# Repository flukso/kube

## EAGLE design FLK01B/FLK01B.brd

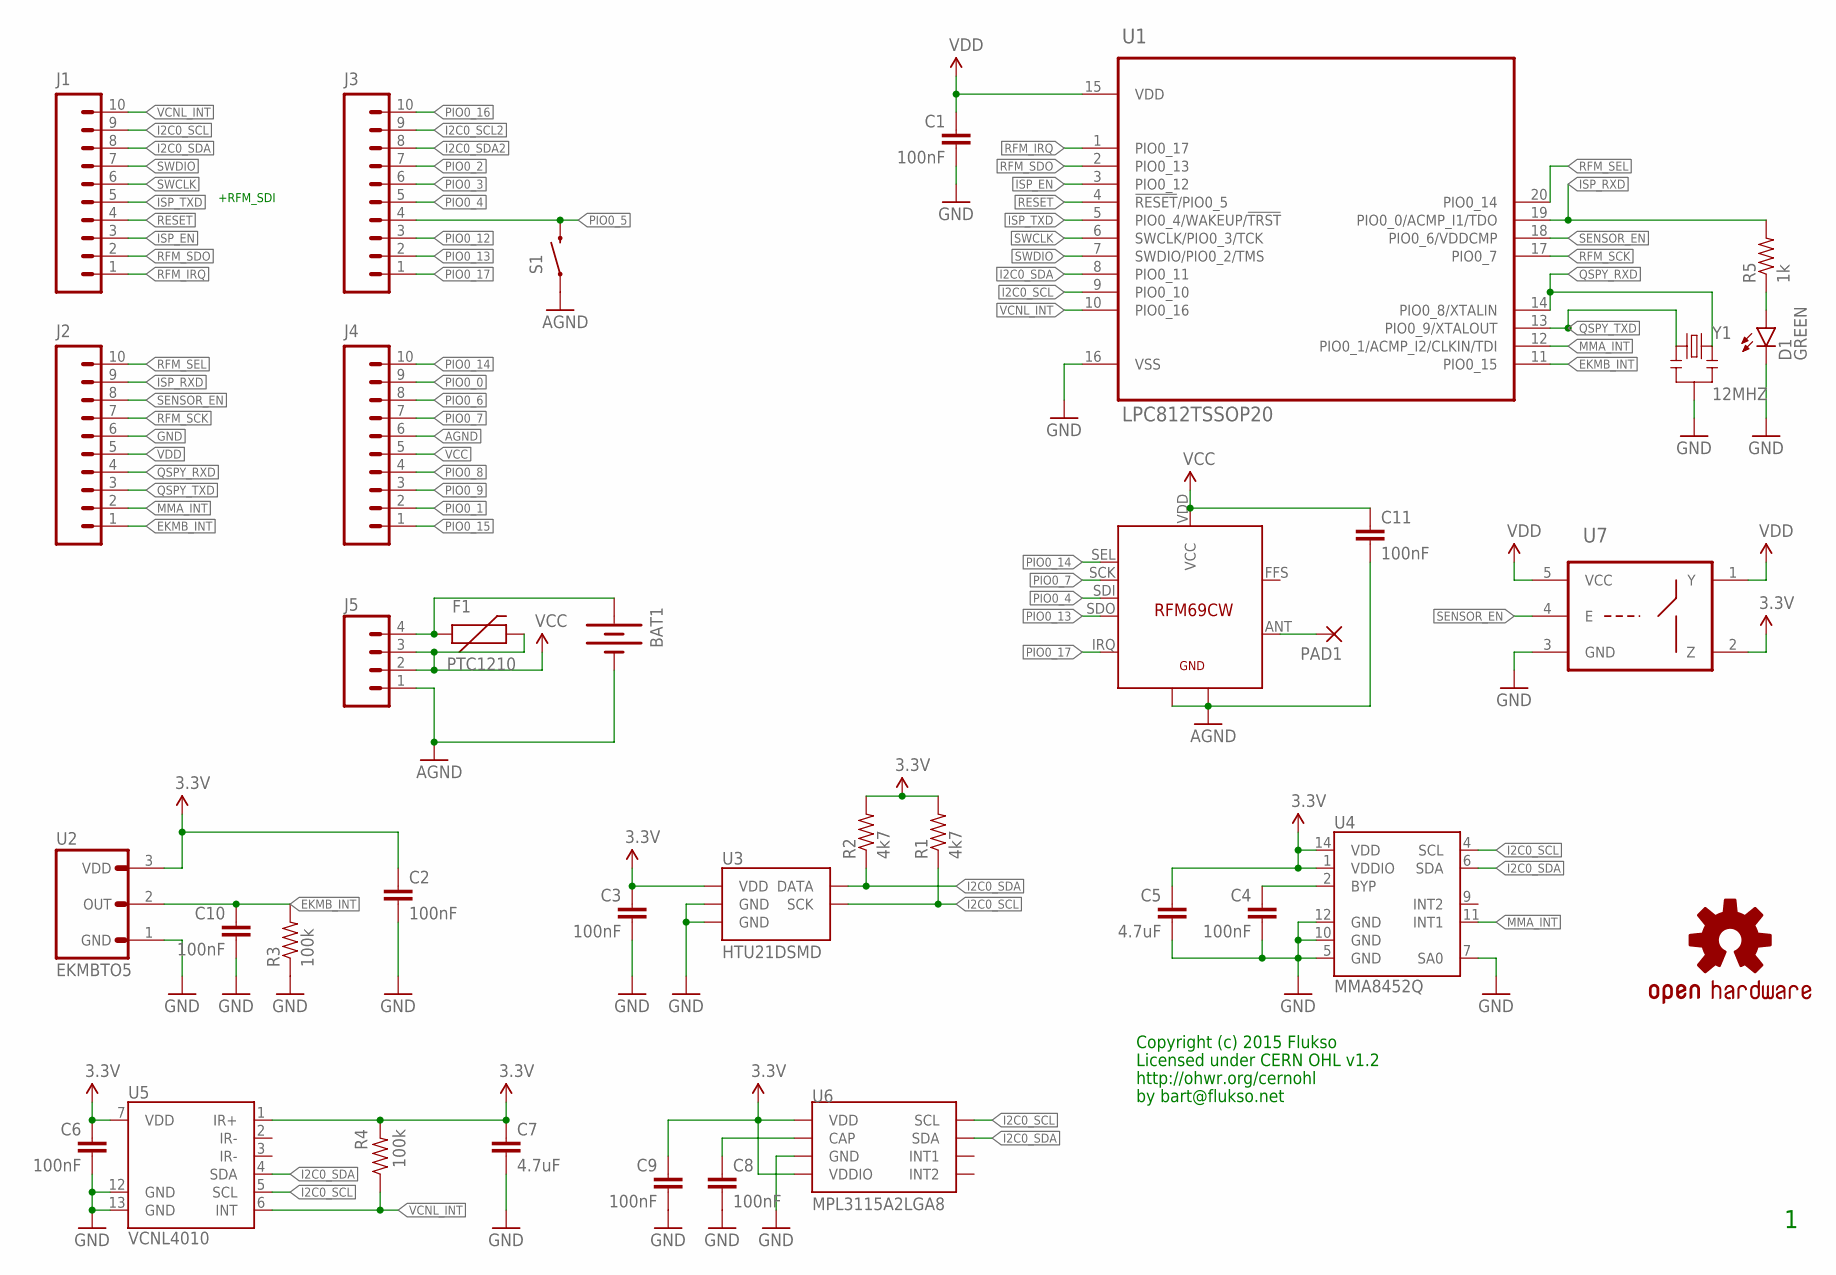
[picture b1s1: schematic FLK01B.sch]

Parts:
BAT1: BATTERY245PTH; BATTCON_245MM_PTH
C1, C2, C3, C4, C6, C8, C9, C10, C11: 100nF; 0402-CAP
C5, C7: 4.7uF; C0805K
D1: GREEN; LED-0603
F1: PTC1210; 1210
J1, J2: M10SMD_MALE_SHORT; 1X10_SMD_MALE_SHORT
J3, J4: M10SMD_FEMALE_SHORT; 1X10_SMD_FEMALE_SHORT
J5: M041X04_NO_SILK; 1X04_NO_SILK
PAD1: WIREPAD_1,6/0,8
R1, R2: 4k7; 0402-RES
R3, R4: 100k; 0402-RES
R5: 1k; 0402-RES
S1: SWITCH-MOMENTARY-2SMD; TACTILE_SWITCH_SMD
U1: LPC812TSSOP20; TSSOP20
U2: EKMBTO5; TO5
U3: HTU21DSMD; HTU21D
U4: MMA8452Q; QFN-16_0.5MM
U5: VCNL4010
U6: MPL3115A2LGA8; LGA8
U7: 741G66; SOT353
U$3: RFM69CW
U$7: OSHW-LOGOS; OSHW-LOGO-S
Y1: 12MHZ; RESONATOR-SMD

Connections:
3.3V: C2.1, C3.1, C5.1, C6.1, C7.1, C9.1, R1.2, R2.2, R4.2, U2.3 (VDD), U3.VDD, U4.1 (VDDIO), U4.14 (VDD), U5.1 (IR+), U5.7 (VDD), U6.1 (VDD), U6.4 (VDDIO), U7.2 (Z)
!ISP_EN!: J1.3, U1.3 (PIO0_12)
!RESET!: J1.4, U1.4 (!RESET!/PIO0_5)
AGND: BAT1.2 (-), C11.2, J4.6, J5.1, S1.1, U$3.GND1, U$3.GND2
EKMB_INT: C10.1, J2.1, R3.2, U1.11 (PIO0_15), U2.2 (OUT)
GND: C1.2, C2.2, C3.2, C4.2, C5.2, C6.2, C7.2, C8.2, C9.2, C10.2, D1.C, J2.6, R3.1, U1.16 (VSS), U2.1 (GND), U3.7 (GND), U3.GND, U4.5 (GND), U4.7 (SA0), U4.10 (GND), U4.12 (GND), U5.12 (GND), U5.13 (GND), U6.3 (GND), U7.3 (GND), Y1.2
I2C0_SCL: J1.9, R1.1, U1.9 (PIO0_10), U3.SCK, U4.4 (SCL), U5.5 (SCL), U6.8 (SCL)
I2C0_SCL2: J3.9
I2C0_SDA: J1.8, R2.1, U1.8 (PIO0_11), U3.DATA, U4.6 (SDA), U5.4 (SDA), U6.7 (SDA)
I2C0_SDA2: J3.8
ISP_RXD: J2.9, R5.2, U1.19 (PIO0_0/ACMP_I1/TDO)
ISP_TXD: J1.5, U1.5 (PIO0_4/WAKEUP/!TRST!)
MMA_INT: J2.2, U1.12 (PIO0_1/ACMP_I2/CLKIN/TDI), U4.11 (INT1)
unnamed: PAD1.1, U$3.ANT
unnamed: BAT1.3 (+), F1.1, J5.4
unnamed: C4.1, U4.2 (BYP)
unnamed: C8.1, U6.2 (CAP)
unnamed: D1.A, R5.1
PIO0_0: J4.9
PIO0_1: J4.2
PIO0_2: J3.7
PIO0_3: J3.6
PIO0_4: J3.5, U$3.SDI
PIO0_5: J3.4, S1.3 (2)
PIO0_6: J4.8
PIO0_7: J4.7, U$3.SCK
PIO0_8: J4.4
PIO0_9: J4.3
PIO0_12: J3.3
PIO0_13: J3.2, U$3.SDO
PIO0_14: J4.10, U$3.SEL
PIO0_15: J4.1
PIO0_16: J3.10
PIO0_17: J3.1, U$3.IRQ
QSPY_RXD: J2.4, U1.14 (PIO0_8/XTALIN), Y1.3
QSPY_TXD: J2.3, U1.13 (PIO0_9/XTALOUT), Y1.1
RFM_IRQ: J1.1, U1.1 (PIO0_17)
RFM_SCK: J2.7, U1.17 (PIO0_7)
RFM_SDO: J1.2, U1.2 (PIO0_13)
RFM_SEL: J2.10, U1.20 (PIO0_14)
SENSOR_EN: J2.8, U1.18 (PIO0_6/VDDCMP), U7.4 (E)
SWCLK: J1.6, U1.6 (SWCLK/PIO0_3/TCK)
SWDIO: J1.7, U1.7 (SWDIO/PIO0_2/TMS)
VCC: C11.1, F1.2, J4.5, J5.2, J5.3, U$3.VDD (VCC)
VCNL_INT: J1.10, R4.1, U1.10 (PIO0_16), U5.6 (INT)
VDD: C1.1, J2.5, U1.15 (VDD), U7.1 (Y), U7.5 (VCC)

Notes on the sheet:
Copyright (c) 2015 Flukso
Licensed under CERN OHL v1.2
http://ohwr.org/cernohl
by bart@flukso.net
+RFM_SDI

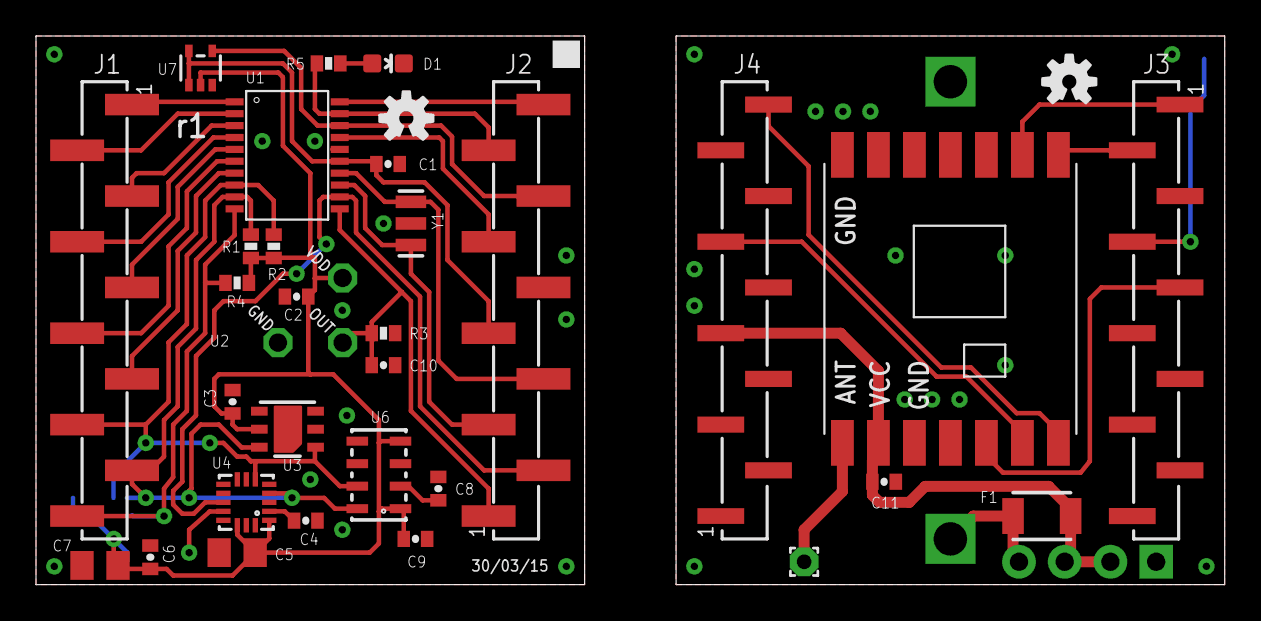
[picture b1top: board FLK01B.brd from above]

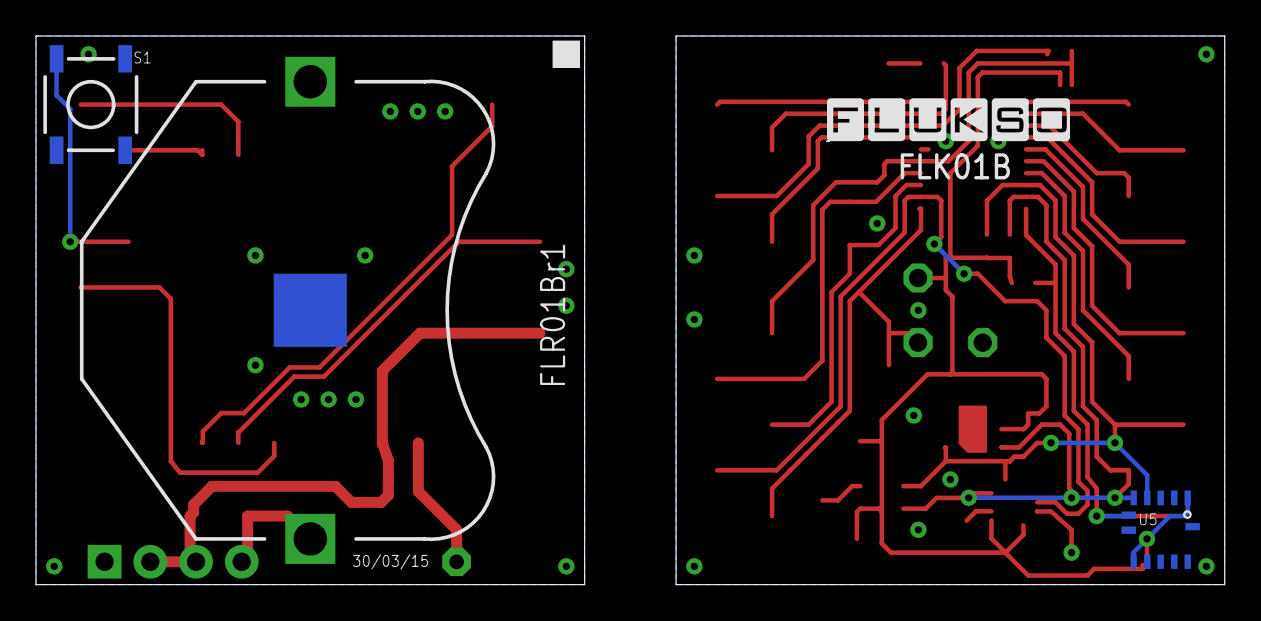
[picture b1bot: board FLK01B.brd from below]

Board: 2 copper layers, 66.0 x 30.5 mm, 38 parts (4 on the bottom side), 34 nets.

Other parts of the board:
U$1: OSHW-LOGOS; OSHW-LOGO-S
U$2: FLUKSO_LOGO_MEDIUM

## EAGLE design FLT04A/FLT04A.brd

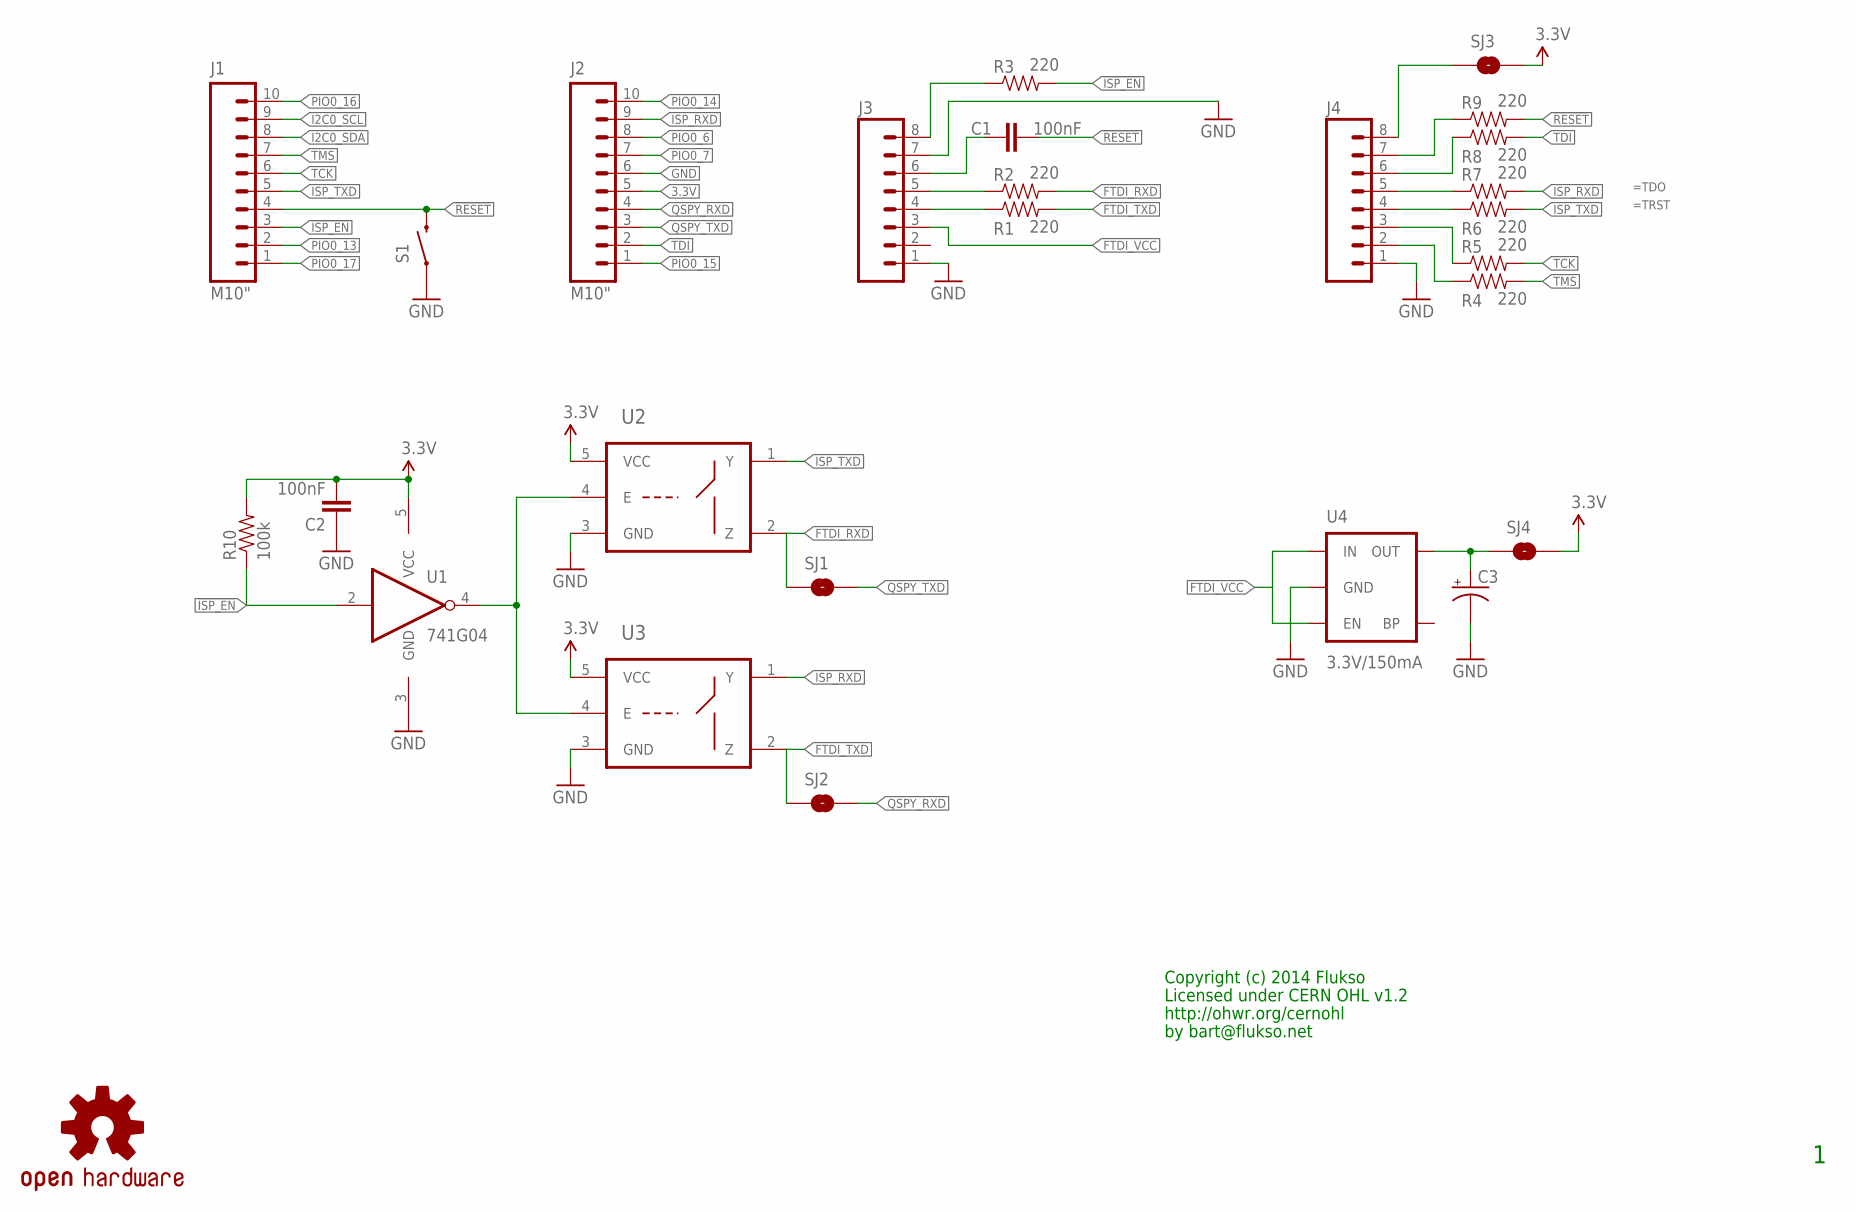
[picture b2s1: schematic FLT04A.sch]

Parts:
C1, C2: 100nF; 0402-CAP
C3: CAP_POL1206; EIA3216
J1, J2: M10"; 1X10
J3, J4: M08; 1X08_PIN1_NO_SILK
R1, R2, R3, R4, R5, R6, R7, R8, R9: 220; 0402-RES
R10: 100k; 0402-RES
S1: SWITCH-MOMENTARY-2SMD; TACTILE_SWITCH_SMD
SJ1, SJ2, SJ3, SJ4: SOLDERJUMPERNC; SJ_2S
U1: 741G04; SOT353
U2, U3: 741G66; SOT353
U4: 3.3V/150mA; SOT23-5
U$1: OSHW-LOGOS; OSHW-LOGO-S

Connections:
3.3V: C2.2, J2.5, R10.2, SJ3.2, SJ4.2, U1.5 (VCC), U2.5 (VCC), U3.5 (VCC)
!ISP_EN!: J1.3, R3.2, R10.1, U1.2 (I)
!RESET!: C1.2, J1.4, R9.2, S1.3 (2)
FTDI_RXD: R2.2, SJ1.1, U2.2 (Z)
FTDI_TXD: R1.2, SJ2.1, U3.2 (Z)
FTDI_VCC: J3.3, U4.1 (IN), U4.3 (EN)
GND: C2.1, C3.C (-), J2.6, J3.1, J3.7, J4.1, S1.1, U1.3 (GND), U2.3 (GND), U3.3 (GND), U4.2 (GND)
I2C0_SCL: J1.9
I2C0_SDA: J1.8
ISP_RXD: J2.9, R7.2, U3.1 (Y)
ISP_TXD: J1.5, R6.2, U2.1 (Y)
unnamed: J3.8, R3.1
unnamed: C1.1, J3.6
unnamed: J3.5, R2.1
unnamed: J3.4, R1.1
unnamed: U1.4 (O), U2.4 (E), U3.4 (E)
unnamed: J4.2, R4.1
unnamed: J4.3, R5.1
unnamed: J4.4, R6.1
unnamed: J4.5, R7.1
unnamed: J4.6, R8.1
unnamed: J4.8, SJ3.1
unnamed: J4.7, R9.1
unnamed: C3.A (+), SJ4.1, U4.5 (OUT)
PIO0_6: J2.8
PIO0_7: J2.7
PIO0_13: J1.2
PIO0_14: J2.10
PIO0_15: J2.1
PIO0_16: J1.10
PIO0_17: J1.1
QSPY_RXD: J2.4, SJ2.2
QSPY_TXD: J2.3, SJ1.2
TCK: J1.6, R5.2
TDI: J2.2, R8.2
TMS: J1.7, R4.2

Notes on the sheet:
Copyright (c) 2014 Flukso
Licensed under CERN OHL v1.2
http://ohwr.org/cernohl
by bart@flukso.net
=TDO
=TRST

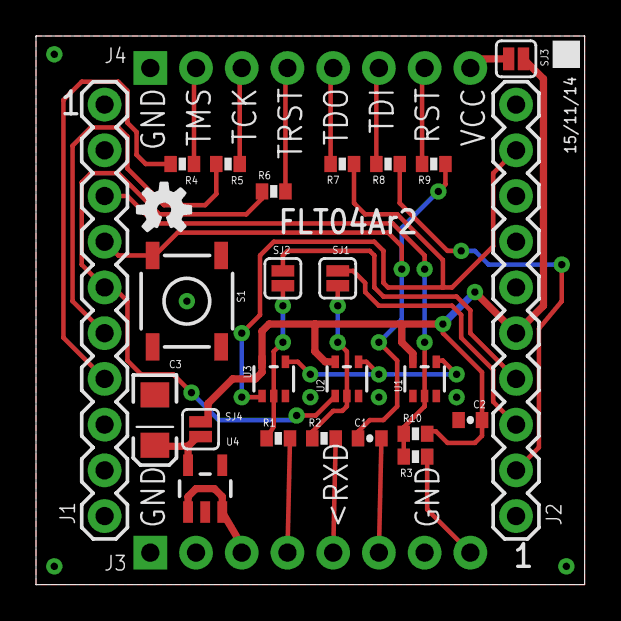
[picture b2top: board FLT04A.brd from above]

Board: 2 copper layers, 30.5 x 30.5 mm, 27 parts (0 on the bottom side), 27 nets.

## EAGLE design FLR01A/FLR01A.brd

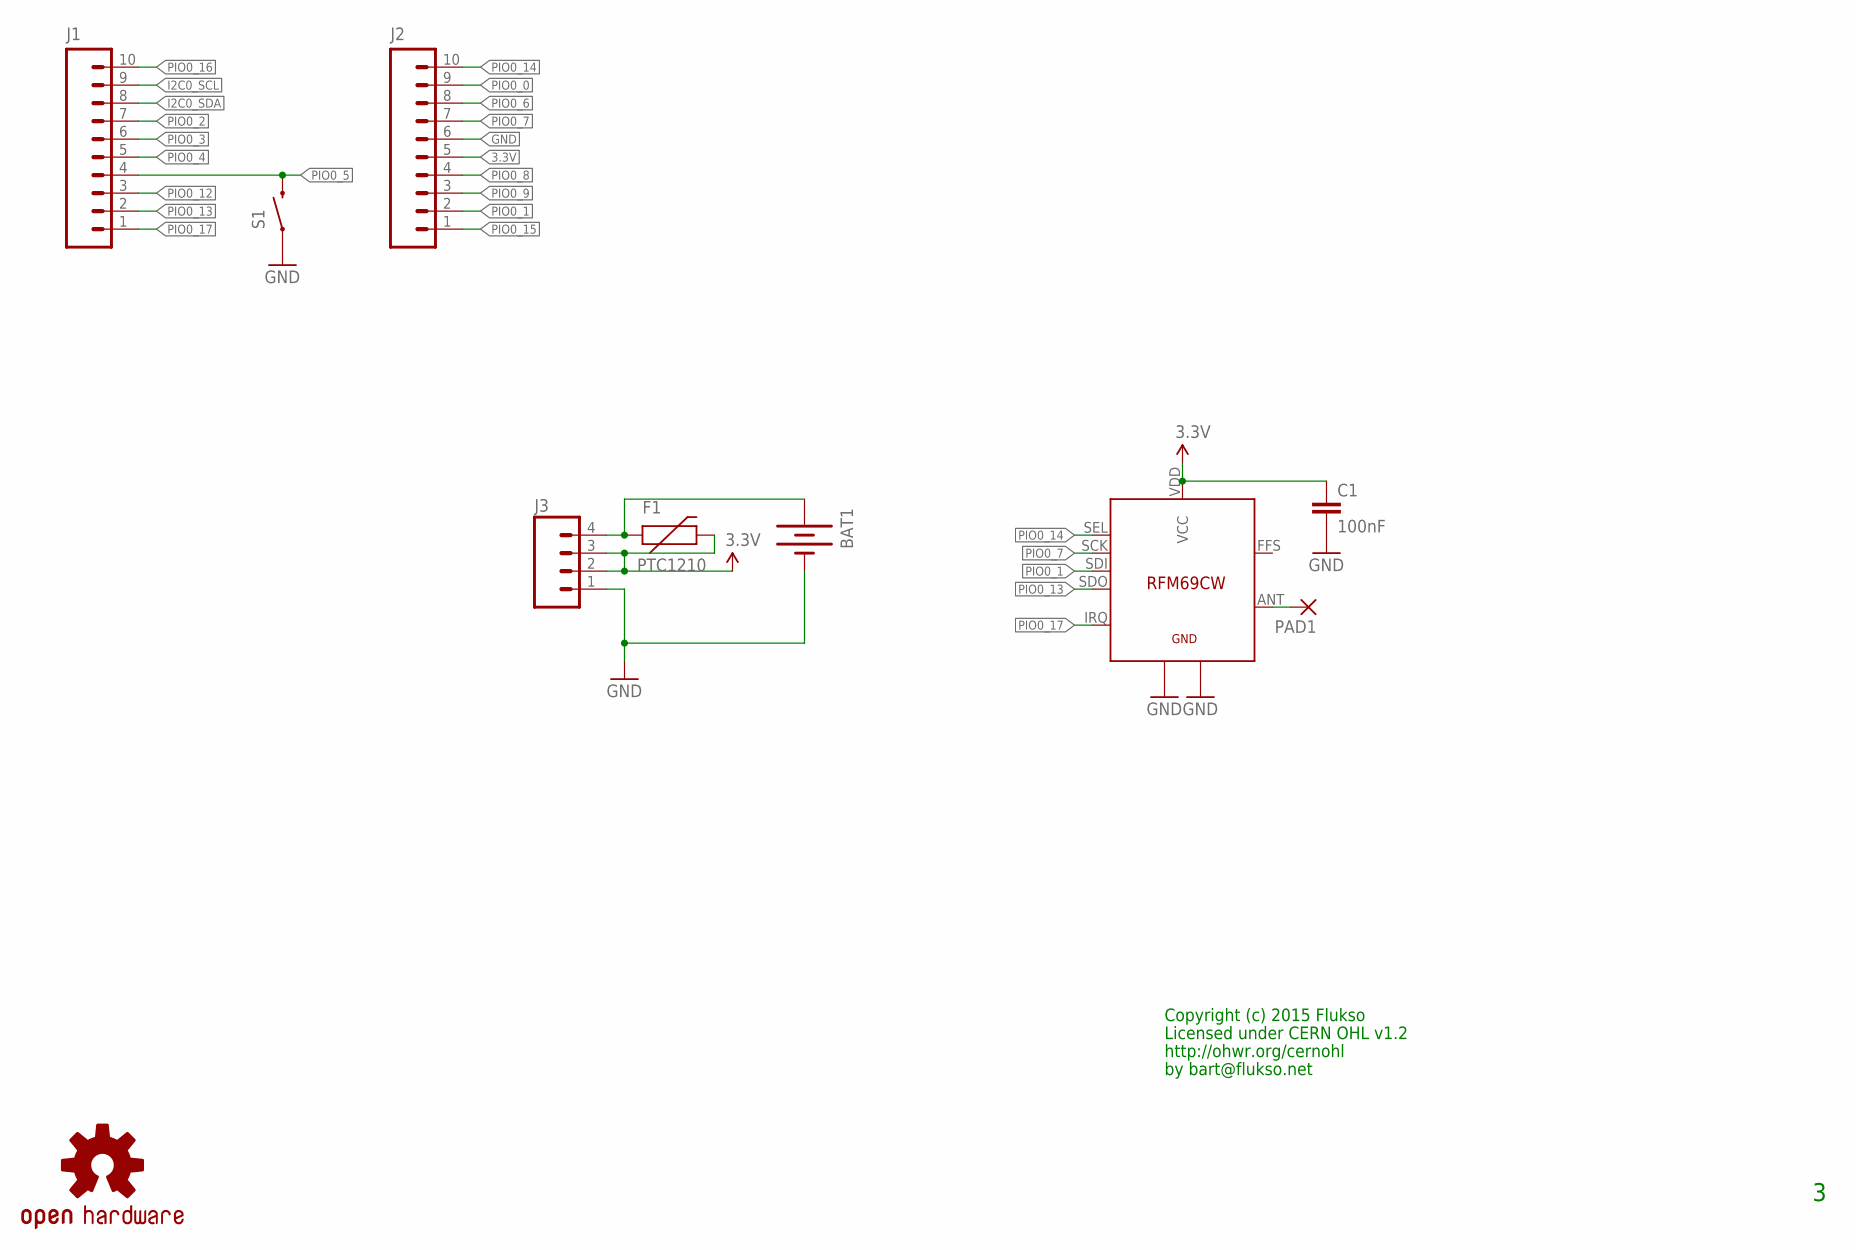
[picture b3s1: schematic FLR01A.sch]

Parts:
BAT1: BATTERY245PTH; BATTCON_245MM_PTH
C1: 100nF; 0402-CAP
F1: PTC1210; 1210
J1, J2: M10SMD_FEMALE_SHORT; 1X10_SMD_FEMALE_SHORT
J3: M041X04_NO_SILK; 1X04_NO_SILK
PAD1: WIREPAD_1,6/0,8
S1: SWITCH-MOMENTARY-2SMD; TACTILE_SWITCH_SMD
U$1: OSHW-LOGOS; OSHW-LOGO-S
U$2: RFM69CW

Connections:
3.3V: C1.1, F1.2, J2.5, J3.2, J3.3, U$2.VDD (VCC)
GND: BAT1.2 (-), C1.2, J2.6, J3.1, S1.1, U$2.GND1, U$2.GND2
I2C0_SCL: J1.9
I2C0_SDA: J1.8
unnamed: BAT1.3 (+), F1.1, J3.4
unnamed: PAD1.1, U$2.ANT
PIO0_0: J2.9
PIO0_1: J2.2, U$2.SDI
PIO0_2: J1.7
PIO0_3: J1.6
PIO0_4: J1.5
PIO0_5: J1.4, S1.3 (2)
PIO0_6: J2.8
PIO0_7: J2.7, U$2.SCK
PIO0_8: J2.4
PIO0_9: J2.3
PIO0_12: J1.3
PIO0_13: J1.2, U$2.SDO
PIO0_14: J2.10, U$2.SEL
PIO0_15: J2.1
PIO0_16: J1.10
PIO0_17: J1.1, U$2.IRQ

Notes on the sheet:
Copyright (c) 2015 Flukso
Licensed under CERN OHL v1.2
http://ohwr.org/cernohl
by bart@flukso.net

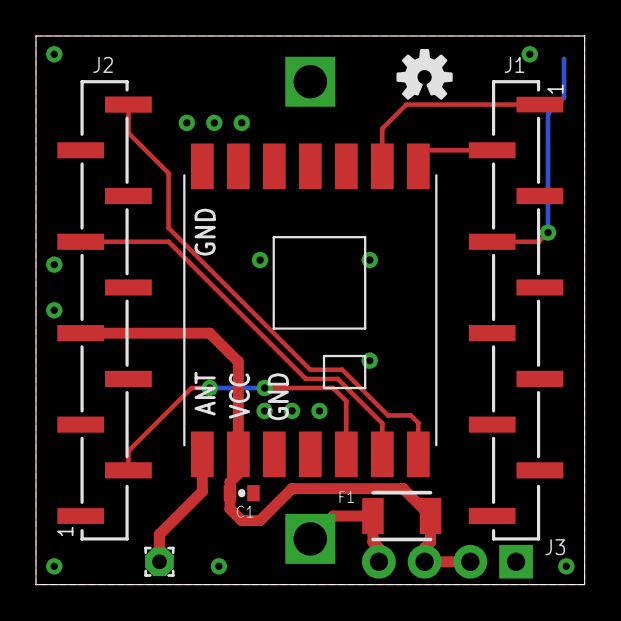
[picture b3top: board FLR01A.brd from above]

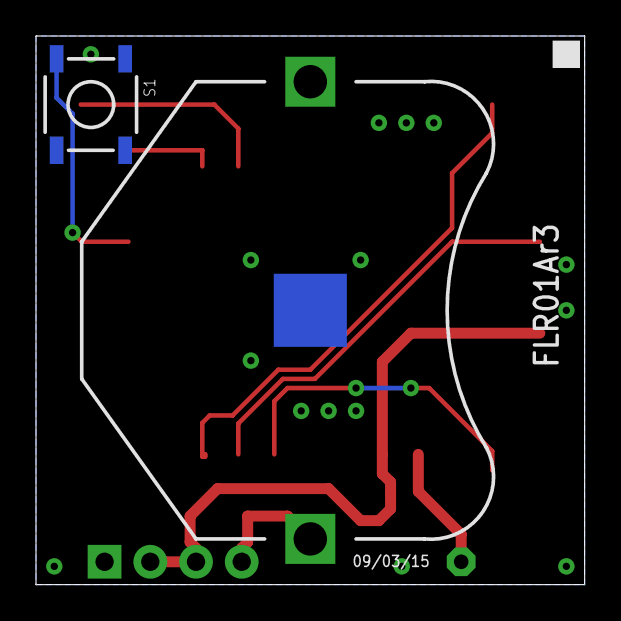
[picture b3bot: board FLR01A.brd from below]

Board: 2 copper layers, 30.5 x 30.5 mm, 10 parts (2 on the bottom side), 10 nets.

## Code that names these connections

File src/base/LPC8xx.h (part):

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  */

typedef struct {                            /*!< (@ 0x40044000) IOCONFIG Structure     */
  __IO uint32_t PIO0_17;                    /*!< (@ 0x40044000) I/O configuration for pin PIO0_17 */
  __IO uint32_t PIO0_13;                    /*!< (@ 0x40044004) I/O configuration for pin PIO0_13 */
  __IO uint32_t PIO0_12;                    /*!< (@ 0x40044008) I/O configuration for pin PIO0_12 */
  __IO uint32_t PIO0_5;                     /*!< (@ 0x4004400C) I/O configuration for pin PIO0_5 */
  __IO uint32_t PIO0_4;                     /*!< (@ 0x40044010) I/O configuration for pin PIO0_4 */
  __IO uint32_t PIO0_3;                     /*!< (@ 0x40044014) I/O configuration for pin PIO0_3 */
  __IO uint32_t PIO0_2;                     /*!< (@ 0x40044018) I/O configuration for pin PIO0_2 */
  __IO uint32_t PIO0_11;                    /*!< (@ 0x4004401C) I/O configuration for pin PIO0_11 */
  __IO uint32_t PIO0_10;                    /*!< (@ 0x40044020) I/O configuration for pin PIO0_10 */
  __IO uint32_t PIO0_16;                    /*!< (@ 0x40044024) I/O configuration for pin PIO0_16 */
  __IO uint32_t PIO0_15;                    /*!< (@ 0x40044028) I/O configuration for pin PIO0_15 */
  __IO uint32_t PIO0_1;                     /*!< (@ 0x4004402C) I/O configuration for pin PIO0_1 */
  __IO uint32_t Reserved;                   /*!< (@ 0x40044030) I/O configuration for pin (Reserved) */
  __IO uint32_t PIO0_9;                     /*!< (@ 0x40044034) I/O configuration for pin PIO0_9 */
  __IO uint32_t PIO0_8;                     /*!< (@ 0x40044038) I/O configuration for pin PIO0_8 */
  __IO uint32_t PIO0_7;                     /*!< (@ 0x4004403C) I/O configuration for pin PIO0_7 */
  __IO uint32_t PIO0_6;                     /*!< (@ 0x40044040) I/O configuration for pin PIO0_6 */
  __IO uint32_t PIO0_0;                     /*!< (@ 0x40044044) I/O configuration for pin PIO0_0 */
  __IO uint32_t PIO0_14;                    /*!< (@ 0x40044048) I/O configuration for pin PIO0_14 */
} LPC_IOCON_TypeDef;
/*@}*/ /* end of group LPC8xx_IOCON */

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
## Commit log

2014-01-07 [eagle] first exercise
2014-01-22 [scad] first enclosure iteration in openscad
2014-01-22 [scad] parameterize kube dimensions
2014-01-22 [scad] add kube scaling factor
2014-01-22 [scad] use support + ring for fixing the magnet
2014-01-22 [scad] pretty print parameters
2014-01-25 [scad] lower base thickness to wall_w
2014-01-25 [scad] increase ring tolerance
2014-01-25 [scad] reduce wall thickness to 1mm
2014-01-26 [scad] go for a hollow support
2014-01-26 [scad] add a small hole for pushing out the pcb
2014-10-23 [src] copy over microbuilder-based LPC81xx code from jeeboot commit 218b6a
2014-10-23 [lpc21isp] wipe the entire flash before isp
2014-10-23 [make] clean up firmware.* as well
2014-10-23 [repo] add a .gitignore to the src dir
2014-10-23 Add grace period for fast OOB ack + resending rqst
    Allow grace period when receiving a fast OOB ack:
    A boot server can take more than 250ms to reply, especially to a pairing
    request. When the boot server replies with a fast OOB ack (CTL and ACK bits
    on, zero payload length), the boot loader is informed that its request is being
    processed. It can therefore introduce a grace period by extending the 250ms
    timeout to 2.5secs. If no such fast OOB ack is received, the original timeout
2014-10-25 [debug] connect CLKOUT to PIO0_3
2014-10-25 [base] change -O from s to 2 to fix memset compilation error
2014-10-25 [debug] add i2c init and basic htu21d comms
2014-10-27 [htu21d] poll user register every second
2014-10-27 [htu21d] add temp and humid measurements
2014-10-28 [debug] sleep now triggers a power down
2014-10-30 [i2c] swap SDA and SCL pins again
2014-10-31 [i2c] group i2c handler vars into a struct
2014-11-01 [led] disable internal pull-up on led pin
2014-11-02 [dbg] add a DEBUG compilation switch
2014-11-02 [clkout] disable pull-up on pin 3
2014-11-08 [wfi] enable sleeponexit mode
2014-11-08 [mv] debug -> flk01a
2014-11-08 [wkt] wake up approx every second
2014-11-08 [ekmb] store counter in GPREG0
2014-11-09 [ekmb] clear interrupt status at init
2014-11-09 [boot] put the radio to sleep at the end of boot
2014-11-09 [boot] correctly configure pull-ups to minimize power consumption
2014-11-09 [spin] guard against overflow condition
2014-11-09 [cfg] load config written by bootloader
2014-11-09 [rfm] tx readings to the mother station
2014-11-10 [boot] trigger a reset every 2^16 secs
2014-11-11 [rfm] enable standby/powerdown modes in sendWait
2014-11-11 [clkout] disable in production
2014-11-11 [rfm] limit tx power to 10dBm
2014-11-11 [pwr] put M0+ in low current mode
2014-11-11 [boot] configure led pin
2014-11-11 [i2c] increase timeout tenfold
2014-11-11 [i2c] reset i2c block at init
2014-11-11 [rfm] put the radio to sleep right after init
2014-11-11 [htu21d] sample every 64sec
2014-11-12 [htu21d] send a reading at startup
2014-11-15 [pcb] kick off rev2
2014-11-15 [pcb] rename FLQ01A to FLK01A
2014-11-15 [pcb] clarify pin functions
2014-11-15 [pcb] re-assign sensor interrupt pins
2014-11-15 [pcb] increase C5 size from 0603 to 0805
2014-11-15 [pcb] correct HTU21D footprint
2014-11-15 [pcb] rename passives
2014-11-16 [pcb] update board layout
2014-11-16 [pcb] use smaller + round pads for I2C header
2014-11-16 [flt] add pull-up to ISP_EN pin
2014-11-16 [flr] update RFM69 silkscreen
2014-11-16 [flr] add ptc fuse in series with battery
2014-11-16 [flr] improve pcb routing
2014-11-22 [i2c] clear the bus on error
2014-11-23 [boot] put RFM_SDO pin in repeater mode
2014-12-06 [acmp] initial implementation
2014-12-06 [acmp] feed vdd to the ladder
2014-12-07 [acmp] change acmp_sample signature
2014-12-14 [i2c] switch to interrupt-driven communication
2014-12-14 [rfm] switch to a 868.3MHz center frequency
2014-12-14 [pkt] send extra Vbatt byte
2014-12-15 [rfm] add spi pinassigns to app sw
2014-12-16 [rfm] insert 16clk delays in spi communication
2015-01-07 [spi] slow down the spi clk to 1MHz
2015-01-07 [rfm] settle on a 19.2kHz bit rate / 868.3 center freq
2015-01-07 [boot] return -1 on reply timeout
2015-02-12 [vcnl4000] read out product id
2015-02-13 [*] split up code into multiple files
2015-02-14 [vcnl4k] enable ambient light sampling
2015-02-14 [vcnl4k] rename vcnl4000 to vcnl4k
2015-02-15 [mpl3115] add support for pressure readings
2015-02-16 [i2c] compact debugging string
2015-02-16 [mma8452] add initial whoami call
2015-02-16 [i2c] define sensor ids in their respective header files
2015-02-17 [mma8452] enable transient detection
2015-02-28 [wwdt] enable the wwdt in the application code
2015-03-05 [dbg] only enable vcnl, mpl and mma in debugging mode for now
2015-03-05 [sample] return to 64sec interval
2015-03-07 [mma8452] increase transient detection sensitivity
2015-03-07 [wwdt] log watchdog event as bit 8 in error byte
2015-03-09 [flk/flr] introduce r3 of sensor and radio board
2015-03-14 [flk/flr] adapt board layout to new M10 footprints + power switch
2015-03-15 [flk] connect VCNL4010 int pin to LPC812
2015-03-15 [flt] 10uF cap did not connect to GND
2015-04-01 [flk/r] fusion of sensor and radio board
2015-07-14 [flk/r] minor changes to layout
2015-07-14 [src] rename flk01a dir to flk01
2015-07-14 [htu21d] increase sampling time
2015-07-14 [lint] add splint-based lint checking make target
2015-07-14 [config] move cfg object definition from header to main
2015-07-14 [style] add indent-based style checking target
2015-07-14 [style] adhere to a linux kernel coding style variant
2015-07-15 [flk01b] move SPI0_MOSI function from pin 1 to 4
2015-07-15 [flk01b] move MMA_INT from pin 16 to 1
2015-07-15 [flk01b] VCNL_INT connects to pin 16
2015-07-26 [mma8452] init accelerometer and send dedicated packet
2015-07-26 [i2c] init I2C_PARAM_T differently to remove memset dependency with -Os
2015-07-26 [mpl+vcnl] add light and pressure readings to gauge packet
2015-07-27 [mma8452] add mma i2c check to error bitfield
2015-07-27 [flk01b] bootloader now uses b-version id by default
2015-07-27 [make] remove firmware dependency from isp target
2015-07-27 [pkt] shrink gauge packet payload size from 12 bytes to 10
2015-07-27 [mma8452] set the accelerometer to low-power mode
2015-07-27 [pkt] split off packet generation into pkt.c
2015-07-28 [acmp] add BOD check to acmp_sample function
2015-07-28 [pkt] shave 3bytes off mma8452 packet
2015-07-28 [pkt] pack gauge readings into a 9-byte payload
2015-07-30 [boot] put rfm into sleep mode during exp back-off
2015-09-16 [scad] add ring magnet snap-to-fit
2015-09-26 [pkt] comment packet structure with vstruct string
2015-09-26 [debug] add openocd stlink v2 cfg script
2016-09-21 [rf69] rf12_canSend will always succeed

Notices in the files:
parts and their libraries:
SparkFun-Passives: Licensing: CC v3.0 Share-Alike You are welcome to use this library for commercial purposes.
